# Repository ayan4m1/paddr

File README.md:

# Paddr

Paddr is a DIY numpad built using [KMK](https://github.com/KMKfw/kmk_firmware). It has four RGB LEDs and seventeen keys.

## Schematic

## Board

## PCB

[OSH Park](https://oshpark.com/shared_projects/GSJlJusC)

## BOM

| Vendor    | Part                                                                                                                                            | Quantity |
| --------- | ----------------------------------------------------------------------------------------------------------------------------------------------- | -------- |
| onsemi    | [1N4148 Diode](https://www.mouser.com/ProductDetail/onsemi-Fairchild/1N4148?qs=i4Fj9T%2FoRm8RMUhj5DeFQg%3D%3D)                                  | 17       |
| Kailh     | [Hotswap Sockets](https://shop.keyboard.io/products/kailh-hotswap-sockets-for-mx-style-keyswitches-x-25)                                        | 17       |
| Adafruit  | [KB2040](https://www.adafruit.com/product/5302)                                                                                                 | 1        |
| Worldsemi | [WS2812B](https://www.adafruit.com/product/1655)                                                                                                | 4        |
| Samsung   | [0.1uF 6.3V Capacitor - 0603](https://www.mouser.com/ProductDetail/Samsung-Electro-Mechanics/CL03A105MQ3CSNH?qs=X6jEic%2FHinBYQpuhNIfduQ%3D%3D) | 4        |

## Assembly

1. Solder the capacitors and LEDs to the bottom of the board.
2. Solder the hotswap sockets to the bottom of the board.
3. Solder the diodes to the top of the board.
4. Solder the KB2040 to the bottom of the board.

## Firmware

Copy all files from the firmware directory to the root of the CIRCUITPY drive. The keymap lives in code.py.

After you install the firmware, the CIRCUITPY drive and USB serial port will be hidden on subsequent restarts of the numpad. To override this behavior, hold down the dash key while plugging the numpad in.

To configure the RGB, double tap the zero key, then tap one of the following buttons:

| Key      | RGB Function   |
| -------- | -------------- |
| 5        | Toggle On/Off  |
| 8        | Value Increase |
| 2        | Value Decrease |
| 4        | Hue Decrease   |
| 6        | Hue Increase   |
| NumLk    | Mode - Solid   |
| Slash    | Mode - Breathe |
| Asterisk | Mode - Rainbow |
| Dash     | Mode - Swirl   |

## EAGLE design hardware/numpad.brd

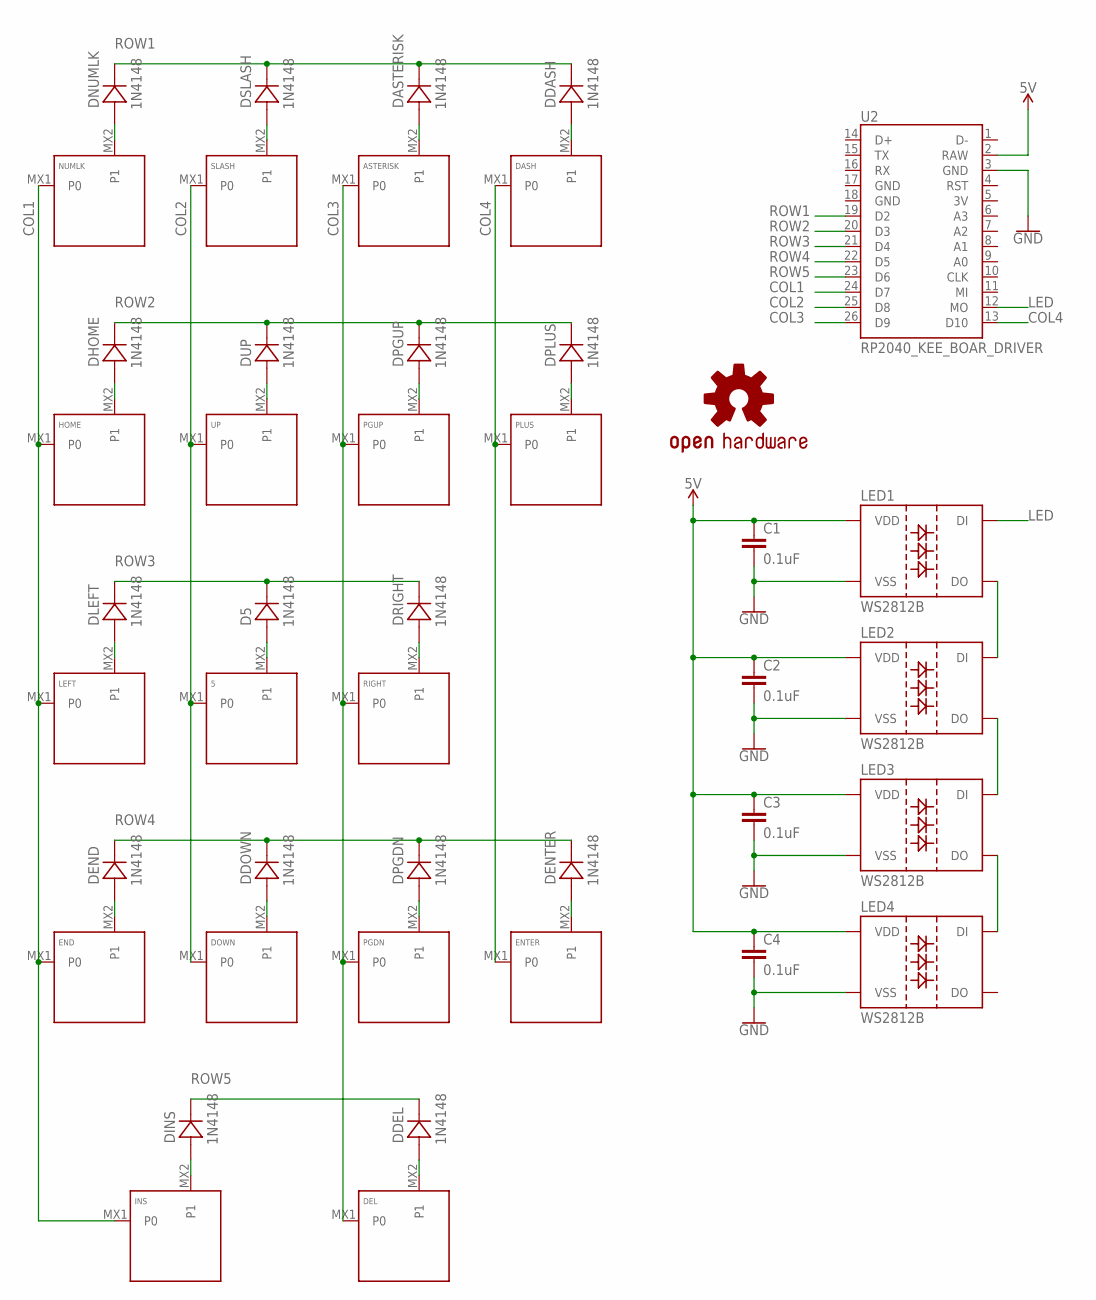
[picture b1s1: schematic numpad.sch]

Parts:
5: KEYSWITCH-PLAIN-MXHSPCB-1U; MXHSPCB-1U
ASTERISK: KEYSWITCH-PLAIN-MXHSPCB-1U; MXHSPCB-1U
C1, C2, C3, C4: 0.1uF; 0603
D5: 1N4148; DO-35
DASH: KEYSWITCH-PLAIN-MXHSPCB-1U; MXHSPCB-1U
DASTERISK: 1N4148; DO-35
DDASH: 1N4148; DO-35
DDEL: 1N4148; DO-35
DDOWN: 1N4148; DO-35
DEL: KEYSWITCH-PLAIN-MXHSPCB-1U; MXHSPCB-1U
DEND: 1N4148; DO-35
DENTER: 1N4148; DO-35
DHOME: 1N4148; DO-35
DINS: 1N4148; DO-35
DLEFT: 1N4148; DO-35
DNUMLK: 1N4148; DO-35
DOWN: KEYSWITCH-PLAIN-MXHSPCB-1U; MXHSPCB-1U
DPGDN: 1N4148; DO-35
DPGUP: 1N4148; DO-35
DPLUS: 1N4148; DO-35
DRIGHT: 1N4148; DO-35
DSLASH: 1N4148; DO-35
DUP: 1N4148; DO-35
END: KEYSWITCH-PLAIN-MXHSPCB-1U; MXHSPCB-1U
ENTER: KEYSWITCH-PLAIN-MXHSPCB-2U-ROTATED; MXHSPCB-2U-ROTATED
HOME: KEYSWITCH-PLAIN-MXHSPCB-1U; MXHSPCB-1U
INS: KEYSWITCH-PLAIN-MXHSPCB-2U; MXHSPCB-2U
LED1, LED2, LED3, LED4: WS2812B
LEFT: KEYSWITCH-PLAIN-MXHSPCB-1U; MXHSPCB-1U
LOGO1: OSHW-LOGOM; OSHW-LOGO-M
NUMLK: KEYSWITCH-PLAIN-MXHSPCB-1U; MXHSPCB-1U
PGDN: KEYSWITCH-PLAIN-MXHSPCB-1U; MXHSPCB-1U
PGUP: KEYSWITCH-PLAIN-MXHSPCB-1U; MXHSPCB-1U
PLUS: KEYSWITCH-PLAIN-MXHSPCB-2U-ROTATED; MXHSPCB-2U-ROTATED
RIGHT: KEYSWITCH-PLAIN-MXHSPCB-1U; MXHSPCB-1U
SLASH: KEYSWITCH-PLAIN-MXHSPCB-1U; MXHSPCB-1U
U2: RP2040_KEE_BOAR_DRIVER
UP: KEYSWITCH-PLAIN-MXHSPCB-1U; MXHSPCB-1U

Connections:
5V: C1.1, C2.1, C3.1, C4.1, LED1.1 (VDD), LED2.1 (VDD), LED3.1 (VDD), LED4.1 (VDD), U2.2 (RAW)
COL1: END.MX1 (P0), HOME.MX1 (P0), INS.MX1 (P0), LEFT.MX1 (P0), NUMLK.MX1 (P0), U2.24 (D7)
COL2: 5.MX1 (P0), DOWN.MX1 (P0), SLASH.MX1 (P0), U2.25 (D8), UP.MX1 (P0)
COL3: ASTERISK.MX1 (P0), DEL.MX1 (P0), PGDN.MX1 (P0), PGUP.MX1 (P0), RIGHT.MX1 (P0), U2.26 (D9)
COL4: DASH.MX1 (P0), ENTER.MX1 (P0), PLUS.MX1 (P0), U2.13 (D10)
GND: C1.2, C2.2, C3.2, C4.2, LED1.3 (VSS), LED2.3 (VSS), LED3.3 (VSS), LED4.3 (VSS), U2.3 (GND)
LED: LED1.4 (DI), U2.12 (MO)
unnamed: DNUMLK.A, NUMLK.MX2 (P1)
unnamed: DSLASH.A, SLASH.MX2 (P1)
unnamed: ASTERISK.MX2 (P1), DASTERISK.A
unnamed: DASH.MX2 (P1), DDASH.A
unnamed: DHOME.A, HOME.MX2 (P1)
unnamed: DUP.A, UP.MX2 (P1)
unnamed: DPGUP.A, PGUP.MX2 (P1)
unnamed: DPLUS.A, PLUS.MX2 (P1)
unnamed: DLEFT.A, LEFT.MX2 (P1)
unnamed: 5.MX2 (P1), D5.A
unnamed: DRIGHT.A, RIGHT.MX2 (P1)
unnamed: DEND.A, END.MX2 (P1)
unnamed: DDOWN.A, DOWN.MX2 (P1)
unnamed: DPGDN.A, PGDN.MX2 (P1)
unnamed: DENTER.A, ENTER.MX2 (P1)
unnamed: DINS.A, INS.MX2 (P1)
unnamed: DDEL.A, DEL.MX2 (P1)
unnamed: LED1.2 (DO), LED2.4 (DI)
unnamed: LED2.2 (DO), LED3.4 (DI)
unnamed: LED3.2 (DO), LED4.4 (DI)
ROW1: DASTERISK.C, DDASH.C, DNUMLK.C, DSLASH.C, U2.19 (D2)
ROW2: DHOME.C, DPGUP.C, DPLUS.C, DUP.C, U2.20 (D3)
ROW3: D5.C, DLEFT.C, DRIGHT.C, U2.21 (D4)
ROW4: DDOWN.C, DEND.C, DENTER.C, DPGDN.C, U2.22 (D5)
ROW5: DDEL.C, DINS.C, U2.23 (D6)

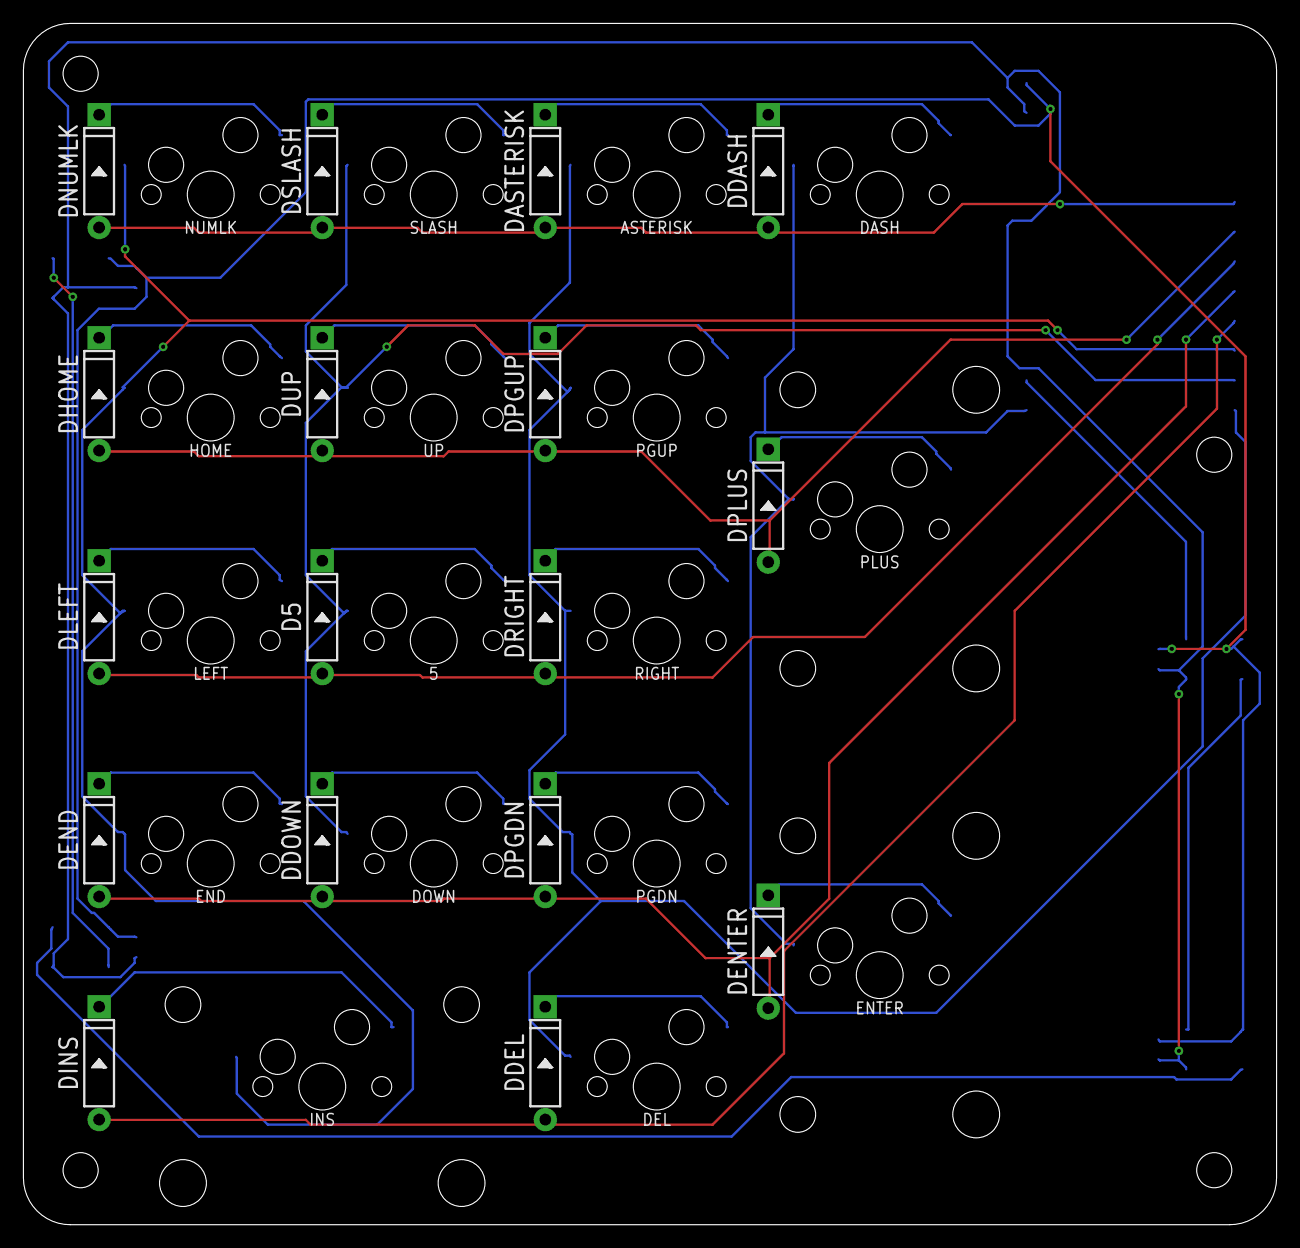
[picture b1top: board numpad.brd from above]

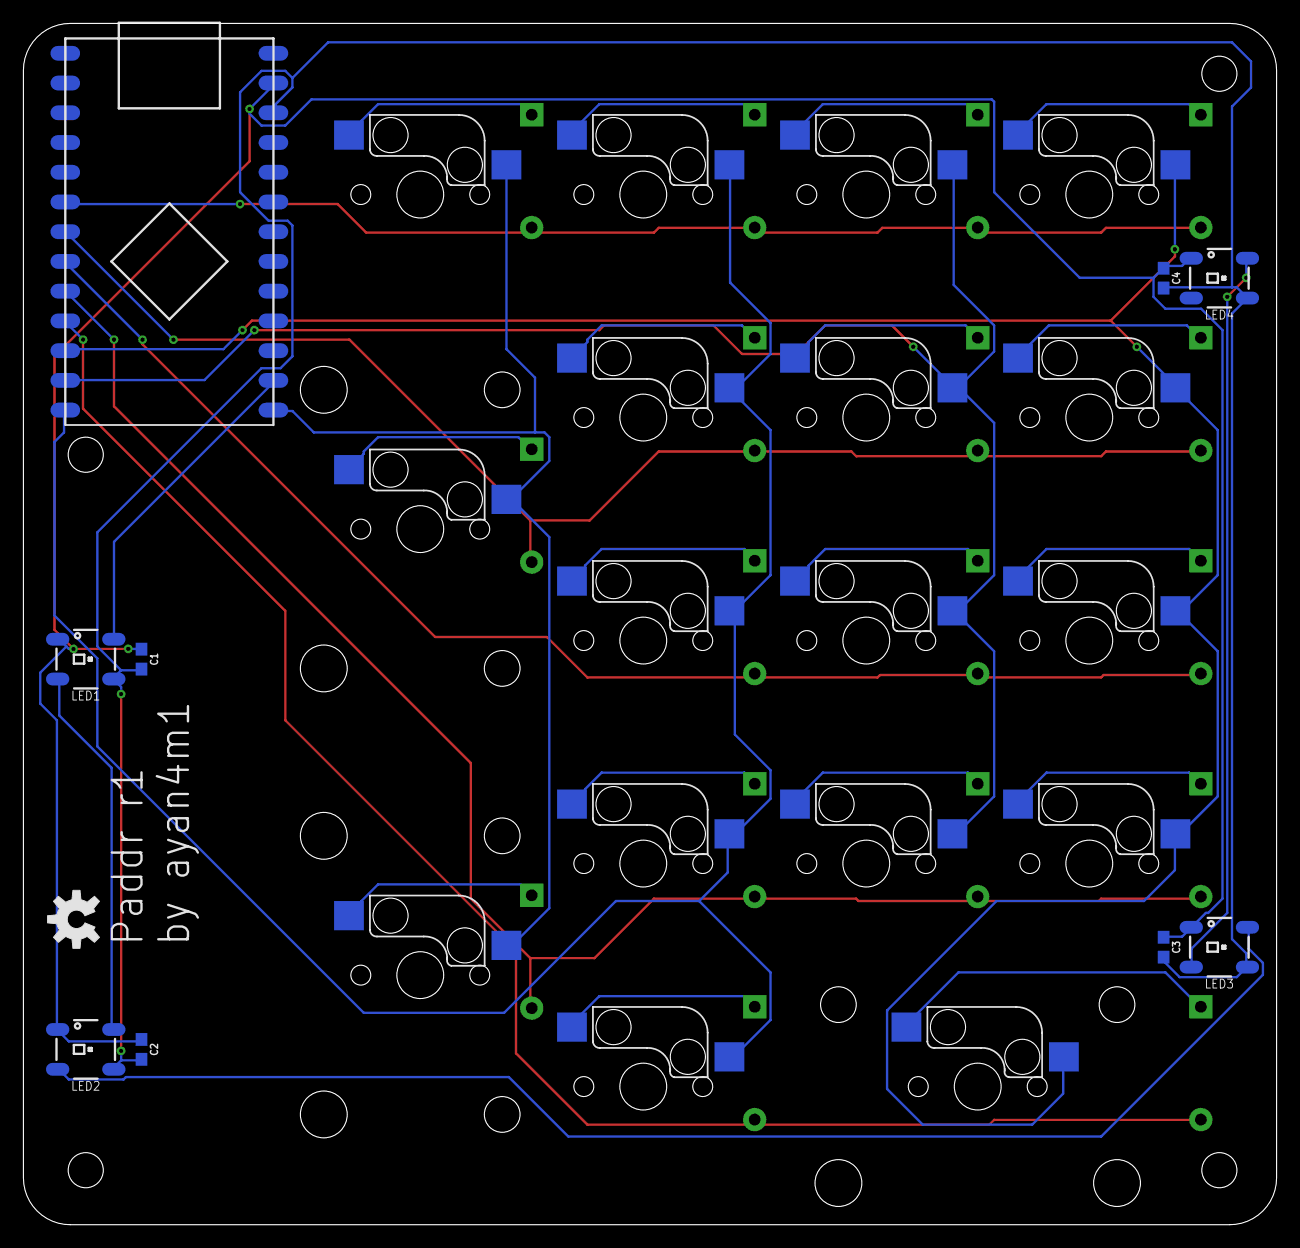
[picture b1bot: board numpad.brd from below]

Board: 2 copper layers, 107.0 x 102.6 mm, 44 parts (26 on the bottom side), 32 nets.

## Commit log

2022-01-23 initial import
2022-01-23 add assembly instructions, capacitor to BOM, and RGB config info
2022-01-23 add line about rgb toggle to README.md

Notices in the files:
parts and their libraries:
SparkFun-Aesthetics: Licensing: Creative Commons ShareAlike 4.0 International - https://creativecommons.org/licenses/by-sa/4.0
